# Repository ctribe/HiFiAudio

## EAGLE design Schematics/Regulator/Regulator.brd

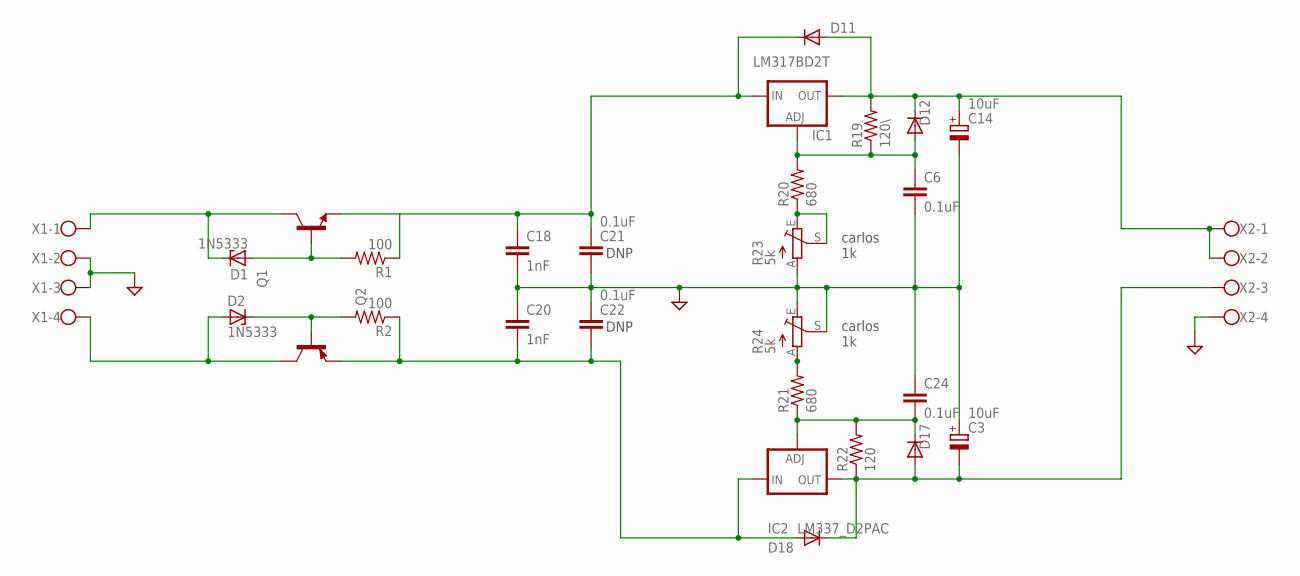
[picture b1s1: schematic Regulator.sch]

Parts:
C3, C14: 10uF; E2,5-6
C6, C21, C22, C24: 0.1uF; C025-025X050
C18, C20: 1nF; C025-025X050
D1, D2: 1N5333; C1702-15
D11, D12, D17, D18: 1N4004
IC1: LM317BD2T; D2PACK
IC2: LM337_D2PAC; D2PACK
Q1: -NPN-TO220V; TO220V
Q2: -PNP-TO220V; TO220V
R1, R2: 100; 0309/12
R19: 120\; 0309V
R20, R21: 680; 0309V
R22: 120; 0309V
R23, R24: 5k; B25P
X1, X2: W237-4

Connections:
GND: C3.+, C6.2, C14.-, C18.2, C20.1, C21.2, C22.1, C24.1, R23.A, R24.E, R24.S, X1.2, X1.3, X2.4
unnamed: D1.A, Q1.1 (B), R1.2
unnamed: C24.2, D17.C, IC2.1 (ADJ), R21.1, R22.2
unnamed: D1.C, Q1.2 (C), X1.1
unnamed: D2.C, Q2.1 (B), R2.2
unnamed: D2.A, Q2.2 (C), X1.4
unnamed: R20.1, R23.E, R23.S
unnamed: R21.2, R24.A
unnamed: C6.1, D12.A, IC1.1 (ADJ), R19.1, R20.2
V15+: C14.+, D11.A, D12.C, IC1.2 (OUT), R19.2, X2.1, X2.2
V15-: C3.-, D17.A, D18.C, IC2.2 (OUT), R22.1, X2.3
V15UN: C18.1, C21.1, D11.C, IC1.3 (IN), Q1.3 (E), R1.1
V-15UN: C20.2, C22.2, D18.A, IC2.3 (IN), Q2.3 (E), R2.1

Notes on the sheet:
DNP
carlos 1k

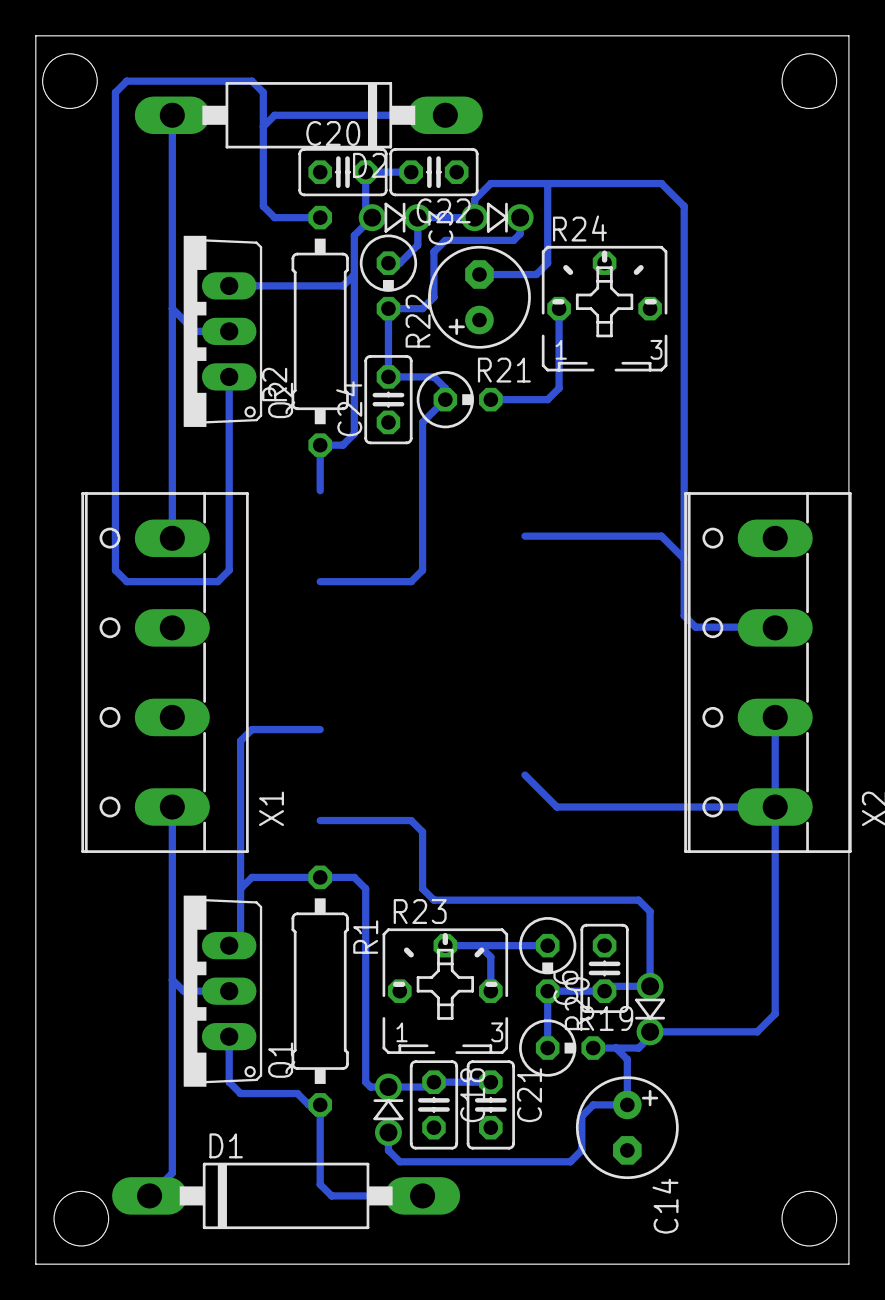
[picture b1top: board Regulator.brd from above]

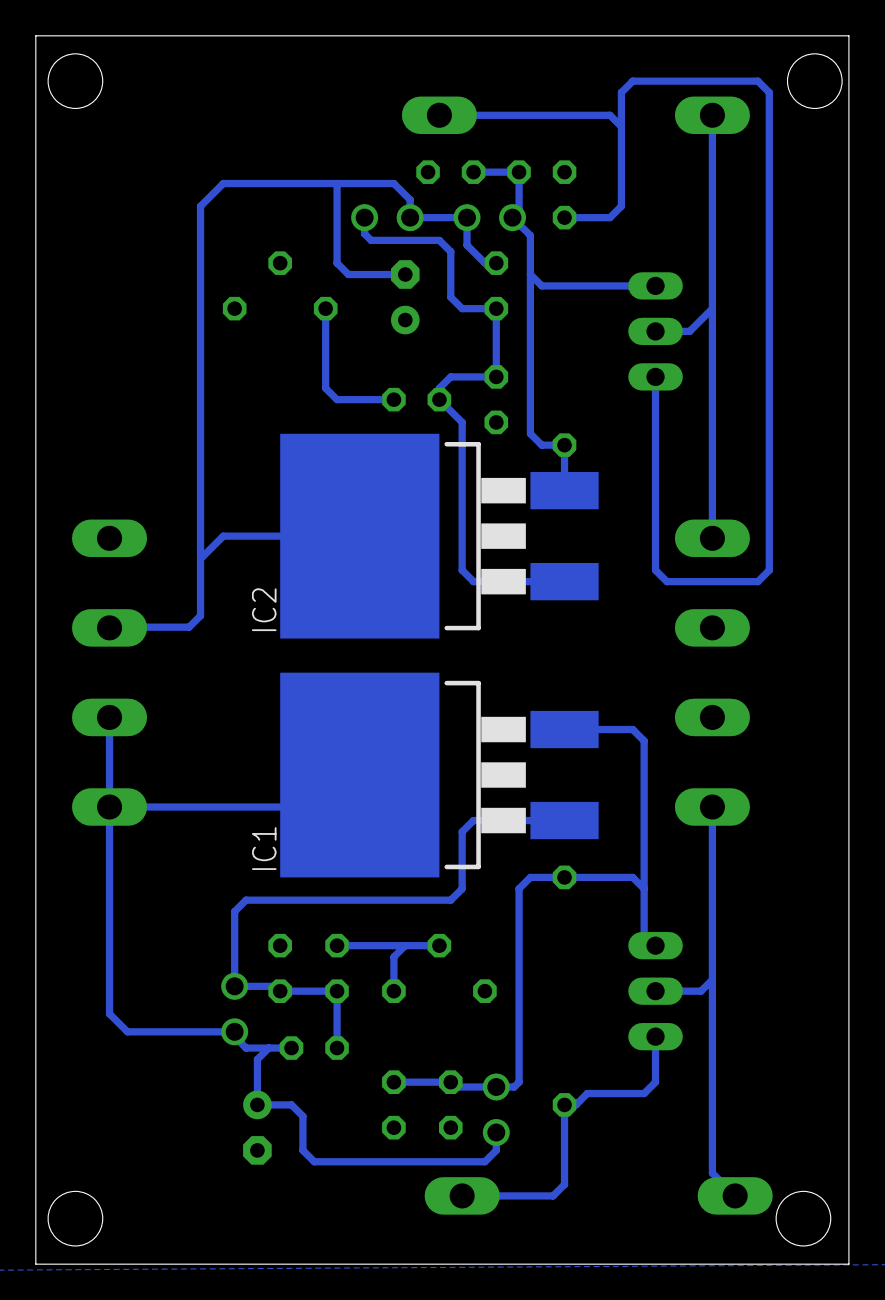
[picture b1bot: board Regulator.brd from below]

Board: 2 copper layers, 45.4 x 68.6 mm, 28 parts (2 on the bottom side), 13 nets.

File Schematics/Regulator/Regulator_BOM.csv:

"Qty";"Value";"Device";"Package";"Parts";"Description";"MF";"MPN";"OC_FARNELL";"OC_NEWARK";
"1";"";"-NPN-TO220V";"TO220V";"Q1";"NPN Transistror";"";"";"";"";
"1";"";"-PNP-TO220V";"TO220V";"Q2";"PNP Transistror";"";"";"";"";
"2";"";"W237-4";"W237-4";"X1, X2";"WAGO SCREW CLAMP";"";"";"unknown";"unknown";
"2";"0.1uF";"C-EU025-025X050";"C025-025X050";"C21, C22";"CAPACITOR, European symbol";"";"";"";"";
"2";"100";"R-US_0309/12";"0309/12";"R1, R2";"RESISTOR, American symbol";"";"";"";"";
"2";"10uF";"C-EU025-025X050";"C025-025X050";"C6, C24";"CAPACITOR, European symbol";"";"";"";"";
"2";"10uF";"CPOL-EUE2.5-6";"E2,5-6";"C3, C14";"POLARIZED CAPACITOR, European symbol";"";"";"";"";
"1";"120";"R-US_0309/V";"0309V";"R22";"RESISTOR, American symbol";"";"";"";"";
"1";"120\";"R-US_0309/V";"0309V";"R19";"RESISTOR, American symbol";"";"";"";"";
"4";"1N4004";"1N4004";"1N4004";"D11, D12, D17, D18";"";"";"";"";"";
"2";"1N5333";"1N5333";"C1702-15";"D1, D2";"Z DIODE";"";"";"";"";
"2";"1nF";"C-EU025-025X050";"C025-025X050";"C18, C20";"CAPACITOR, European symbol";"";"";"";"";
"2";"5k";"TRIM_EU-B25P";"B25P";"R23, R24";"POTENTIOMETER";"";"";"";"";
"2";"680";"R-US_0309/V";"0309V";"R20, R21";"RESISTOR, American symbol";"";"";"";"";
"1";"LM317BD2T";"LM317BD2T";"D2PACK";"IC1";"500 mA Adjustable Output Positive Voltage Regulator";"";"";"";"";
"1";"LM337_D2PAC";"LM337_D2PAC";"D2PACK";"IC2";"";"";"";"";"";

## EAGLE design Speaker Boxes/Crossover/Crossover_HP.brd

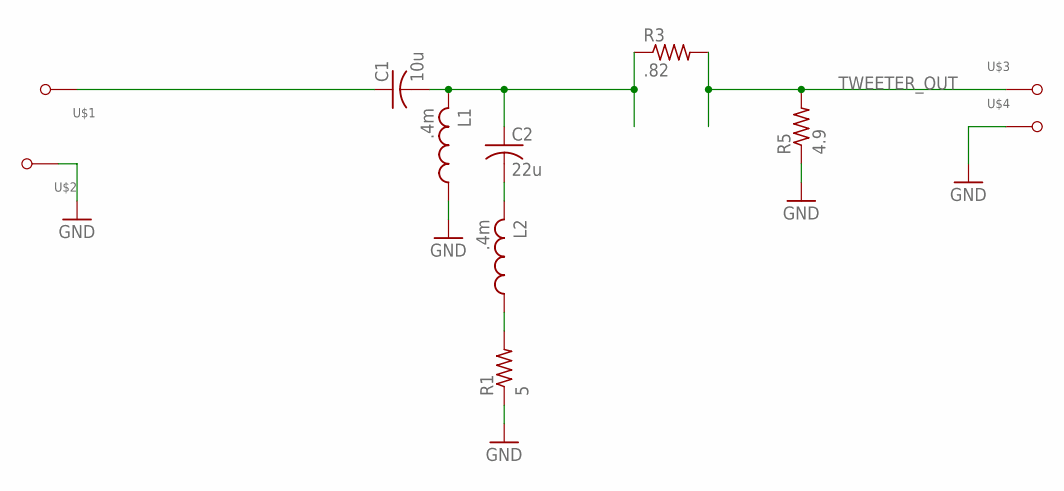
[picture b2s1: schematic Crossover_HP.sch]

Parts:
C1: 10u; 3.5MMP_8MMP
C2: 22u; 5MMP_10MMD
L1, L2: .4m; AIR_COIL_2INX3/4IN
R1: 5; 9.5MMX9MMX22MM
R3: .82; 9.5MMX9MMX48MM
R5: 4.9; 9.5MMX9MMX48MM
U$1, U$2, U$3, U$4: 18AWG_HOLE

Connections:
GND: L1.P$1 (1), R1.P$1 (1), R5.P$1 (1), U$2.P$1, U$4.P$1
unnamed: C1.NEG (2), C2.POS (1), L1.P$2 (2), R3.P$1 (1)
unnamed: C2.NEG (2), L2.P$2 (2)
unnamed: L2.P$1 (1), R1.P$2 (2)
unnamed: C1.POS (1), U$1.P$1
TWEETER_OUT: R3.P$2 (2), R5.P$2 (2), U$3.P$1

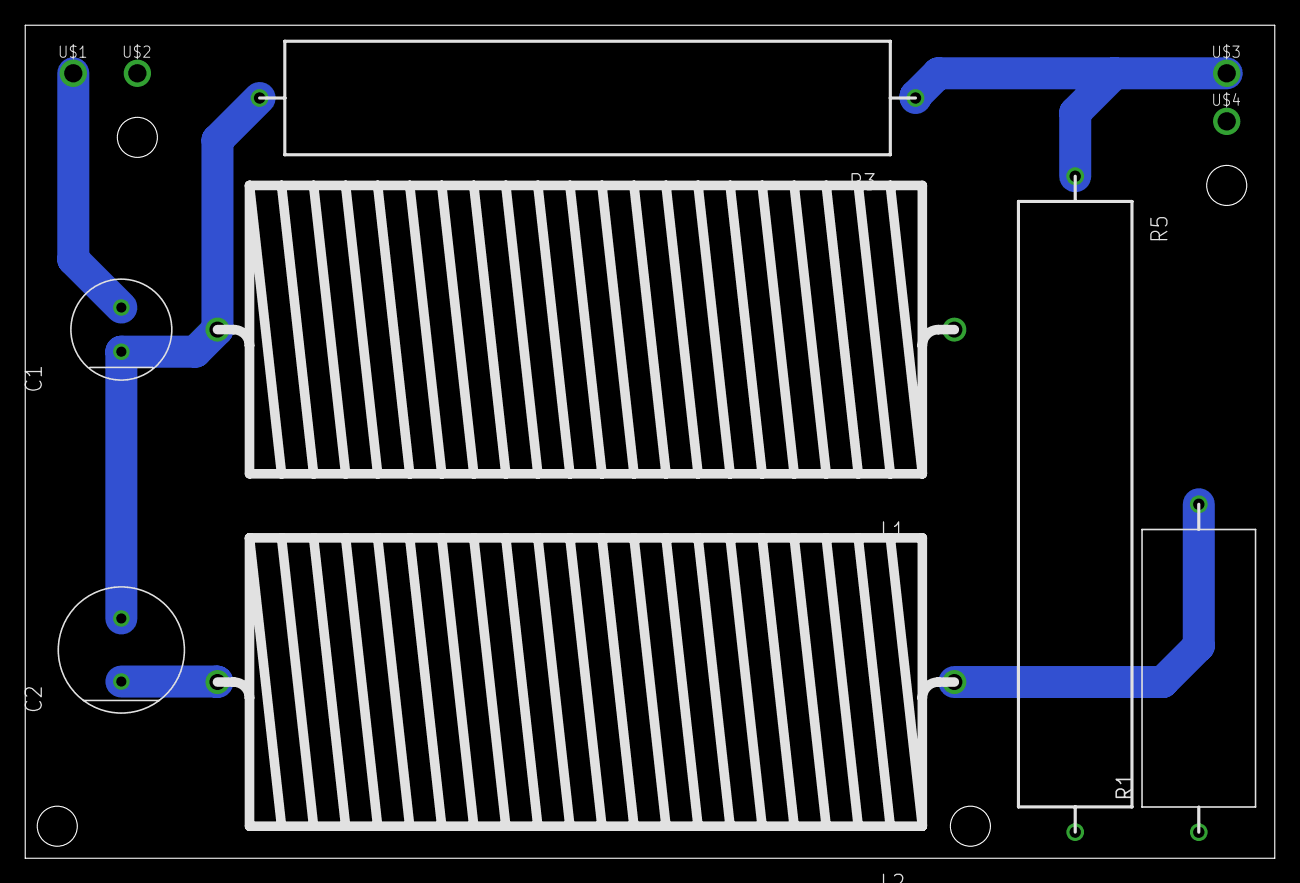
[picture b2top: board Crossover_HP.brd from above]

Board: 2 copper layers, 99.1 x 66.0 mm, 11 parts (0 on the bottom side), 6 nets.

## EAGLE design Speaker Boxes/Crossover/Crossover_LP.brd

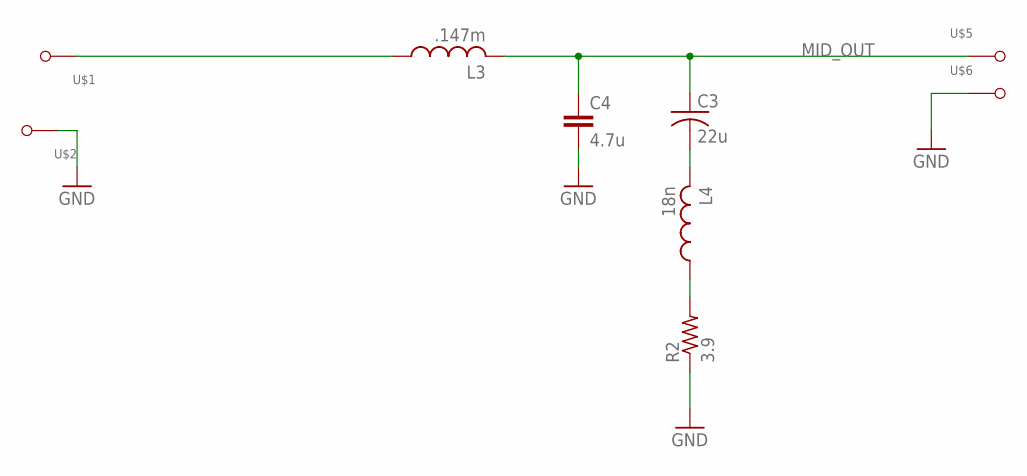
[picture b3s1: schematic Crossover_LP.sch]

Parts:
C3: 22u; 5MMP_10MMD
C4: 4.7u; C225-074X268
L3: .147m; AIR_COIL_2INX3/4IN
L4: 18n; AIR_COIL_2INX3/4IN
R2: 3.9; 9.5MMX9MMX22MM
U$1, U$2, U$5, U$6: 18AWG_HOLE

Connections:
GND: C4.2, R2.P$1 (1), U$2.P$1, U$6.P$1
MID_OUT: C3.POS (1), C4.1, L3.P$2 (2), U$5.P$1
unnamed: L3.P$1 (1), U$1.P$1
unnamed: C3.NEG (2), L4.P$2 (2)
unnamed: L4.P$1 (1), R2.P$2 (2)

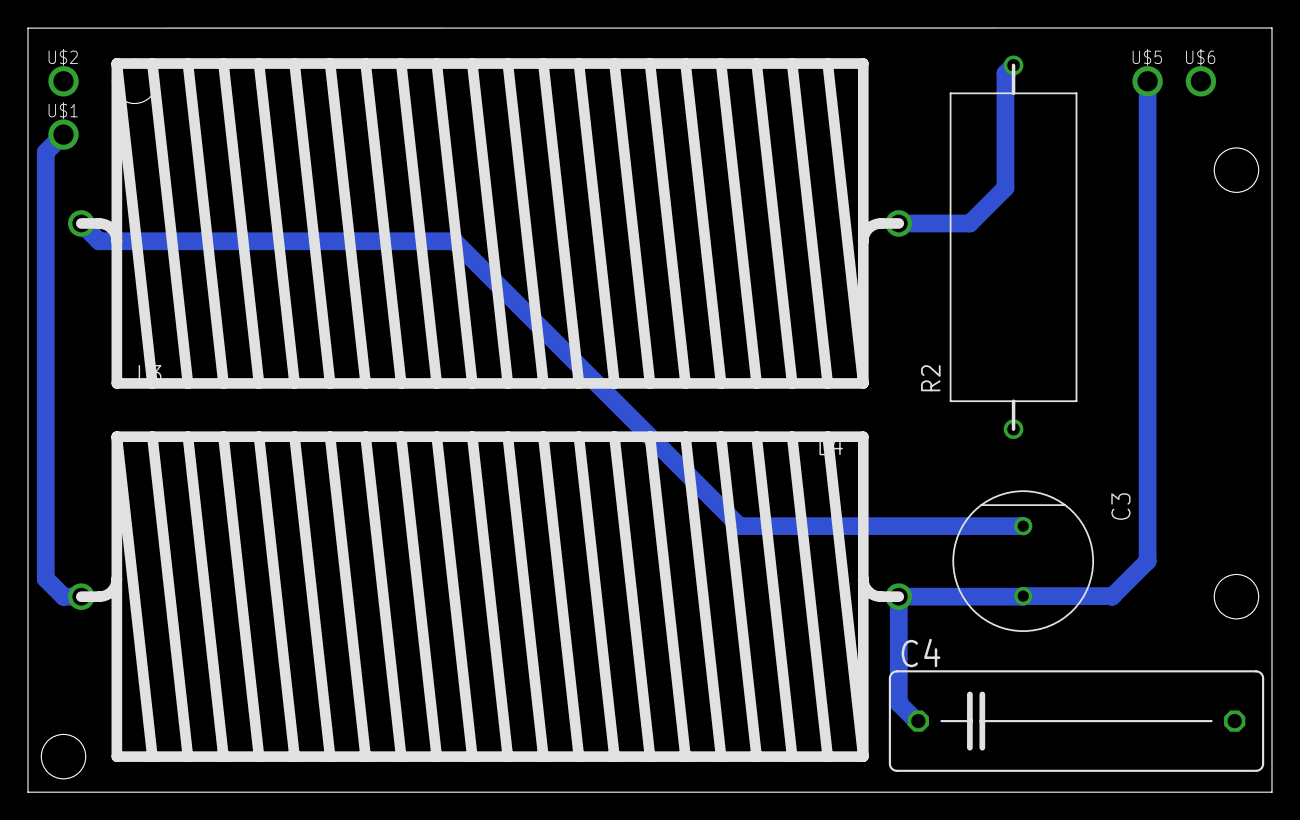
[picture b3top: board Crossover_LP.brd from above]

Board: 2 copper layers, 88.9 x 54.6 mm, 9 parts (0 on the bottom side), 5 nets.

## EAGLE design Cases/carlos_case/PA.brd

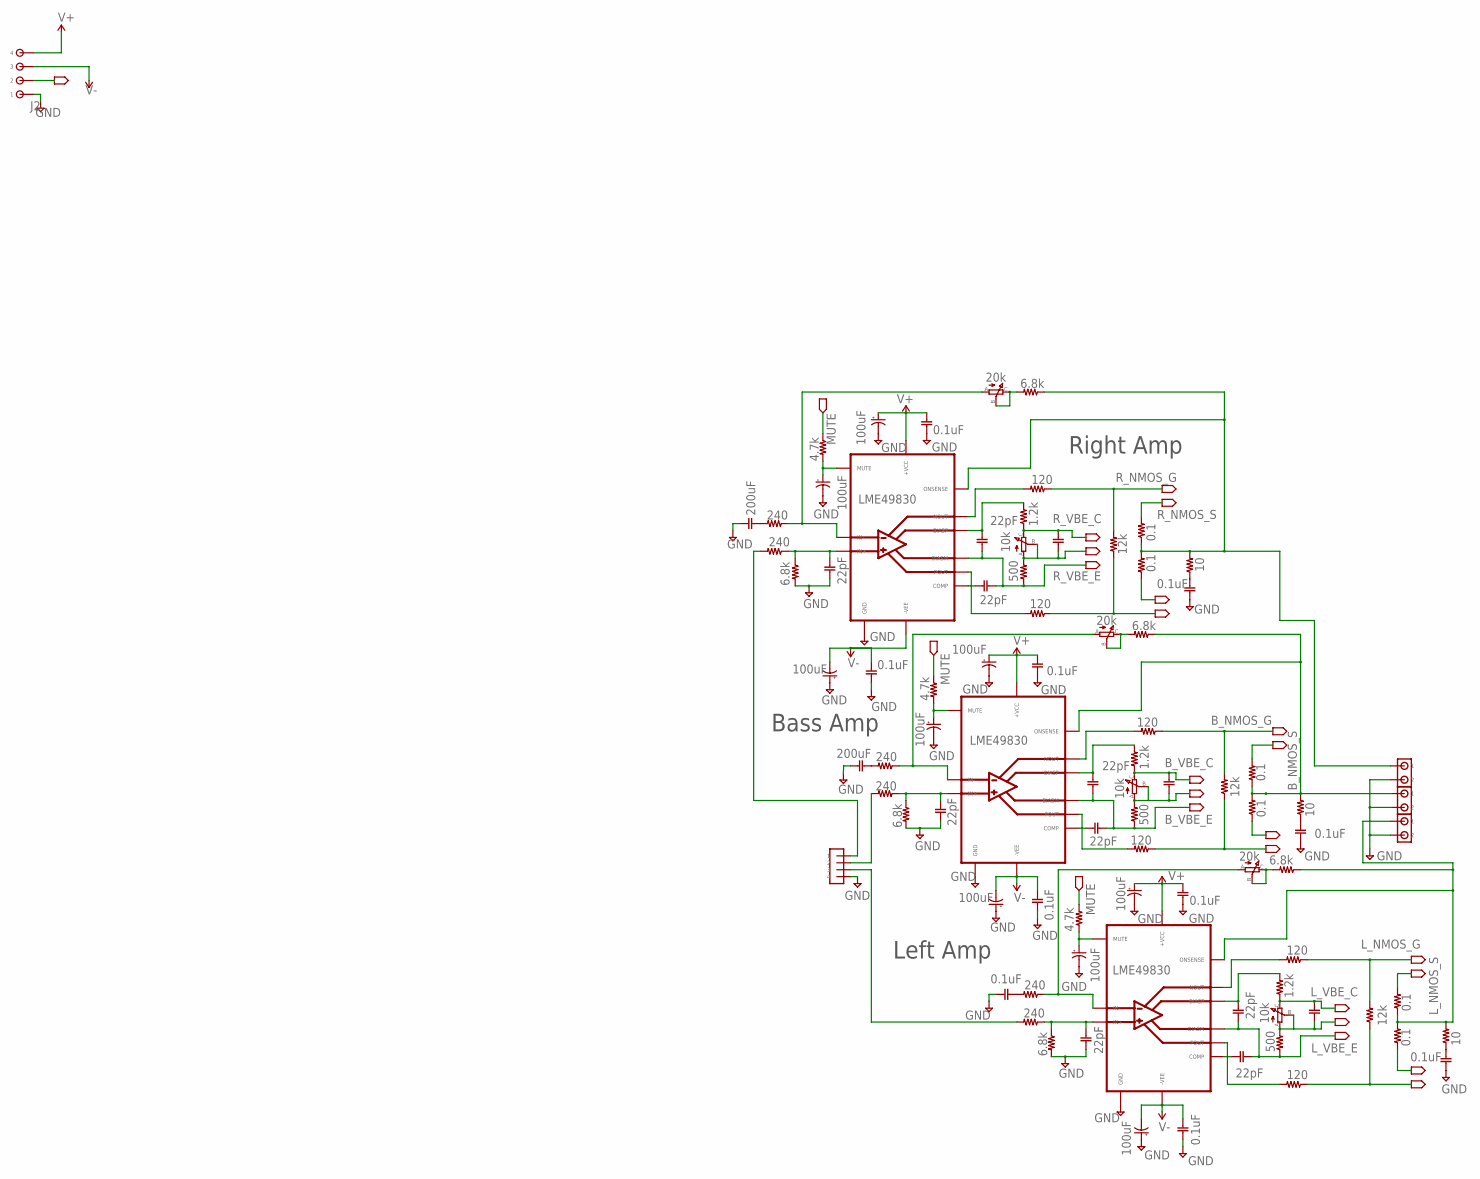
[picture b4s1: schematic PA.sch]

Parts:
C1, C8, C9, C10, C20, C21, C22, C29, C35, C36, C37, C44: 22pF; C050-024X044
C2, C4, C6, C16, C17, C28, C31, C32, C43: 100uF; E2,5-6
C3, C5, C15, C18, C19, C27, C33, C34, C42, C45: 0.1uF; C050-024X044
C7, C30: 200uF; C050-024X044
J1: 4_PIN_AMPCONN; 4_PIN_AMPCON
J2: 1984633
J3, J4, J5: 2TERMINAL_SPEAKER
PR1, PR2, PR3, PR4, PR5, PR6: 0.1; 0617V
R1, R11, R12, R22, R23, R55: 240; 0204V
R2, R10, R13, R21, R24, R56: 6.8k; 0204V
R3, R14, R44: 1.2k; 0204V
R4, R15, R45: 500; 0204V
R5, R16, R46: 12k; 0204V
R6, R7, R17, R18, R47, R48: 120; 0204V
R8, R19, R51: 10; 0309V
R9, R20, R52: 4.7k; 0204V
U1, U2, U3: LME49830; NDN0015A
VR1, VR3, VR5: 20k; EVM2W
VR2, VR4, VR6: 10k; EVM2W

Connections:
BASS_OUT: J4.P$1 (1), PR1.2, PR2.1, R8.2, R13.1, U2.P$8 (ONSENSE)
B_NMOS_G: R5.2, R7.1
B_NMOS_S: PR2.2
B_PMOS_G: R5.1, R6.1
B_PMOS_S: PR1.1
B_VBE_B: C21.1, R4.2, VR4.A, VR4.B
B_VBE_C: C21.2, R3.1, VR4.C
B_VBE_E: C20.1, C22.1, R4.1, U2.P11 (BIASM)
GND: C1.1, C2.+, C3.1, C4.-, C5.2, C6.-, C7.1, C15.1, C16.+, C17.-, C18.1, C19.2, C27.1, C28.-, C29.1, C30.1, C31.+, C32.-, C33.1, C34.2, C42.1, C43.-, C44.1, C45.1, J1.4, J2.P$1 (1), J3.P$2 (2), J4.P$2 (2), J5.P$2 (2), R2.2, R10.2, R21.2, U1.P3 (GND), U2.P3 (GND), U3.P3 (GND)
LEFT_IN: J1.3, R22.2
LEFT_OUT: J5.P$1 (1), PR3.2, PR4.1, R19.2, R24.1, U3.P$8 (ONSENSE)
L_NMOS_G: R16.2, R18.1
L_NMOS_S: PR4.2
L_PMOS_G: R16.1, R17.1
L_PMOS_S: PR3.1
L_VBE_B: C36.1, R15.2, VR6.A, VR6.B
L_VBE_C: C36.2, R14.1, VR6.C
L_VBE_E: C35.1, C37.1, R15.1, U3.P11 (BIASM)
MUTE: J2.P$2 (2), R9.1, R20.1, R52.1
unnamed: J1.2, R11.2
unnamed: J1.1, R1.2
unnamed: C20.2, R3.2, U2.P12 (BIASP)
unnamed: R48.2, U1.P14 (NOUT)
unnamed: C22.2, U2.P6 (COMP)
unnamed: R6.2, U2.P13 (POUT)
unnamed: C27.2, R8.1
unnamed: C28.+, R9.2, U2.P2 (MUTE)
unnamed: R7.2, U2.P14 (NOUT)
unnamed: C1.2, R1.1, R2.1, U1.P4 (IN+)
unnamed: C29.2, R10.1, R11.1, U2.P4 (IN+)
unnamed: C30.2, R12.2
unnamed: R12.1, U2.P5 (IN-), VR3.A
unnamed: R13.2, VR3.B, VR3.C
unnamed: C35.2, R14.2, U3.P12 (BIASP)
unnamed: C37.2, U3.P6 (COMP)
unnamed: R17.2, U3.P13 (POUT)
unnamed: R55.1, U1.P5 (IN-), VR1.A
unnamed: C42.2, R19.1
unnamed: C7.2, R55.2
unnamed: C43.+, R20.2, U3.P2 (MUTE)
unnamed: R18.2, U3.P14 (NOUT)
unnamed: C44.2, R21.1, R22.1, U3.P4 (IN+)
unnamed: R56.2, VR1.B, VR1.C
unnamed: C45.2, R23.2
unnamed: R23.1, U3.P5 (IN-), VR5.A
unnamed: R24.2, VR5.B, VR5.C
unnamed: C8.2, U1.P6 (COMP)
unnamed: C9.2, R44.2, U1.P12 (BIASP)
unnamed: R47.2, U1.P13 (POUT)
unnamed: C15.2, R51.1
unnamed: C6.+, R52.2, U1.P2 (MUTE)
RIGHT_OUT: J3.P$1 (1), PR5.2, PR6.1, R51.2, R56.1, U1.P$8 (ONSENSE)
R_NMOS_G: R46.2, R48.1
R_NMOS_S: PR6.2
R_PMOS_G: R46.1, R47.1
R_PMOS_S: PR5.1
R_VBE_B: C10.1, R45.2, VR2.A, VR2.B
R_VBE_C: C10.2, R44.1, VR2.C
R_VBE_E: C8.1, C9.1, R45.1, U1.P11 (BIASM)
V+: C4.+, C5.1, C17.+, C19.1, C32.+, C34.1, J2.P$4 (4), U1.P15 (+VCC), U2.P15 (+VCC), U3.P15 (+VCC)
V-: C2.-, C3.2, C16.-, C18.2, C31.-, C33.2, J2.P$3 (3), U1.P10 (-VEE), U2.P10 (-VEE), U3.P10 (-VEE)

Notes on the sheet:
Right Amp
Bass Amp
Left Amp

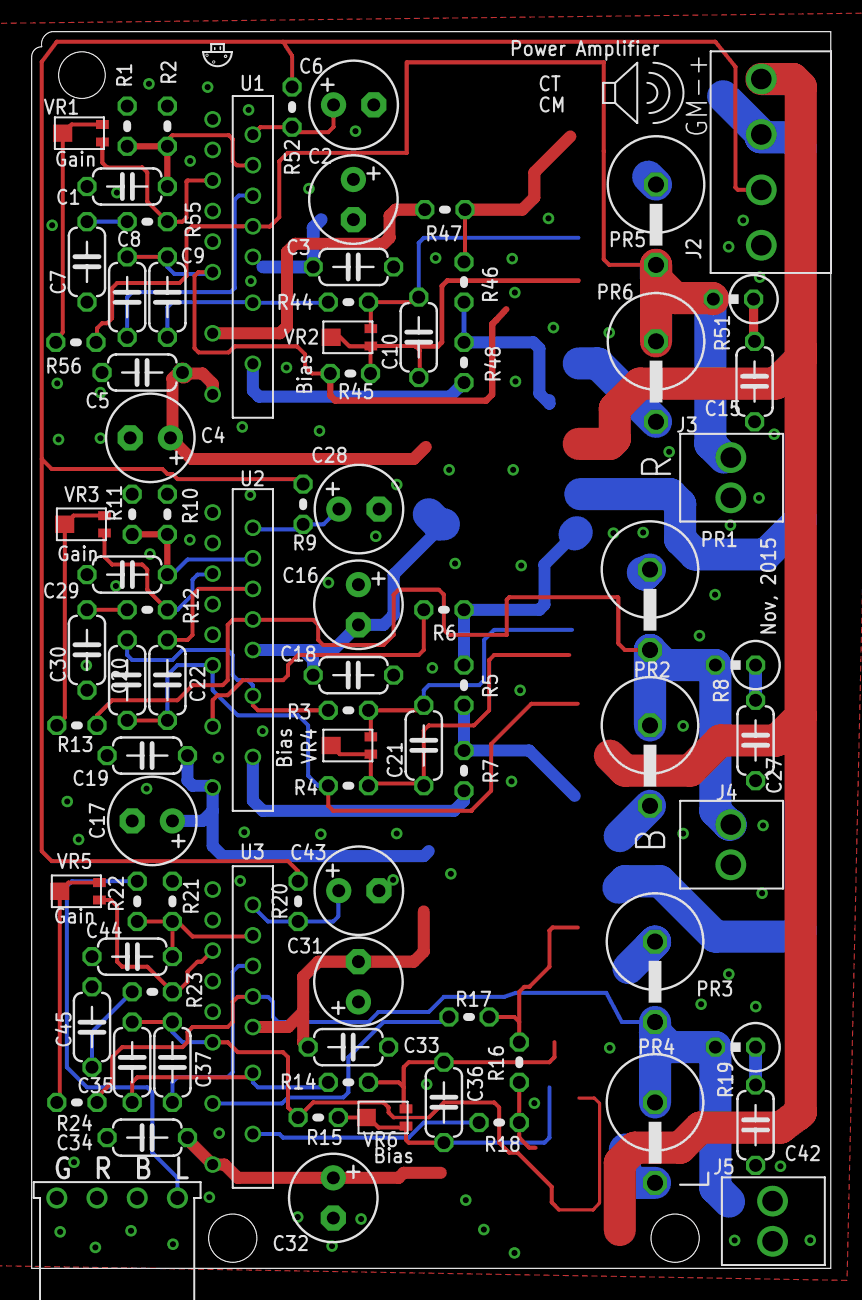
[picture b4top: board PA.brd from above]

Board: 2 copper layers, 50.5 x 78.1 mm, 88 parts (0 on the bottom side), 55 nets.

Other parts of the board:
U$17: MUSHROOM
U$48: SPEAKER

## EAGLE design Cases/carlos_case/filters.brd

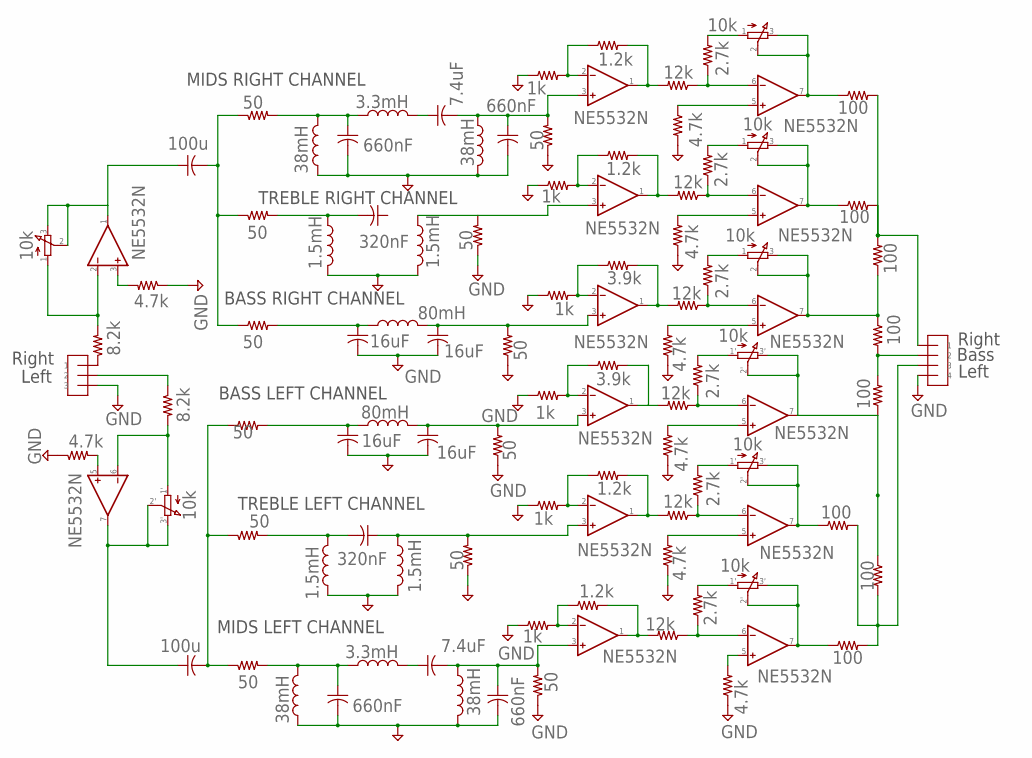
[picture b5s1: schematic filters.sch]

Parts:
C1, C10: 7.4uF; C050-024X044
C2, C3, C11, C12: 660nF; C050-024X044
C4, C9: 320nF; C050-024X044
C5, C6, C7, C8: 16uF; C050-024X044
C13, C14: 100u; C050-024X044
IC1, IC2, IC3, IC4, IC5, IC6, IC7: NE5532N; DIL08
J1: 3_PIN_AMPCONN
J2: 4_PIN_AMPCONN; 4_PIN_AMPCON
L1, L10: 3.3mH; 6000-XXXX-RC
L2, L3, L11, L12: 38mH; 6000-XXXX-RC
L4, L5, L8, L9: 1.5mH; 6000-XXXX-RC
L6, L7: 80mH; 6000-XXXX-RC
R1, R2: 8.2k; 0204V
R3, R4, R9, R10, R14, R15, R22, R23, R27, R28, R31, R32: 50; 0204V
R5, R7, R13, R20, R26, R38: 1k; 0204V
R6, R11, R16, R19, R24, R33: 12k; 0204V
R8, R21: 3.9k; 0204V
R12, R17, R25, R36: 1.2k; 0204V
R18, R29, R30, R34, R35, R37: 2.7k; 0204V
R39, R40, R41, R88, R89, R90, R91, R92: 100; 0204V
R42, R43, R44, R45, R46, R47, R48, R49: 4.7k; 0204V
VR1: 10k; VOL_POT_2GANG
VR2, VR3, VR4: 10k; TONE_POT_2GANG

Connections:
BASS: J2.2, R41.2, R90.2
GND: C2.2, C3.2, C5.2, C6.2, C7.2, C8.2, C11.2, C12.2, J1.3, J2.4, L2.1, L3.2, L4.2, L5.2, L8.1, L9.2, L11.2, L12.1, R3.1, R5.1, R7.1, R10.1, R13.1, R15.1, R20.1, R23.1, R26.1, R28.1, R31.1, R38.1, R42.1, R43.1, R44.2, R45.1, R46.1, R47.1, R48.1, R49.1
LEFT: J2.3, R39.2, R91.2, R92.2
LEFT_IN: J1.2, R2.1
MVO: IC6.7 (OUT), R40.1, R90.1, VR4.2 (1_2), VR4.3 (1_3)
unnamed: IC1.2 (-IN), R1.2, VR1.1
unnamed: C13.1, IC1.1 (OUT), VR1.2, VR1.3
unnamed: IC1.6 (-IN), R2.2, VR1.1' (1)
unnamed: IC2.6 (-IN), R16.1, R18.1
unnamed: C14.1, IC1.7 (OUT), VR1.2' (2), VR1.3' (3)
unnamed: IC6.2 (-IN), R7.2, R8.1
unnamed: C6.1, IC6.3 (+IN), L6.2, R3.2
unnamed: IC3.6 (-IN), R33.1, R37.1
unnamed: IC4.2 (-IN), R12.1, R13.2
unnamed: IC7.1 (OUT), R19.2
unnamed: IC6.6 (-IN), R6.1, R34.1
unnamed: C5.1, L6.1, R4.2
unnamed: C4.2, L5.1, R9.2
unnamed: C8.1, IC7.3 (+IN), L7.2, R31.2
unnamed: IC2.1 (OUT), R16.2, R17.2
unnamed: IC1.3 (+IN), R42.2
unnamed: IC4.1 (OUT), R11.2, R12.2
unnamed: IC4.6 (-IN), R11.1, R35.1
unnamed: IC1.5 (+IN), R43.2
unnamed: IC2.7 (OUT), R88.1, VR2.2 (1_2), VR2.3 (1_3)
unnamed: C13.2, R4.1, R9.1, R14.1
unnamed: C2.1, L1.1, L2.2, R14.2
unnamed: R18.2, VR2.1 (1_1)
unnamed: IC7.6 (-IN), R19.1, R29.1
unnamed: IC2.2 (-IN), R5.2, R17.1
unnamed: IC2.5 (+IN), R44.1
unnamed: C1.1, L1.2
unnamed: C9.2, L8.2, R22.2
unnamed: IC5.5 (+IN), R48.2
unnamed: IC5.1 (OUT), R24.2, R25.2
unnamed: IC5.6 (-IN), R24.1, R30.1
unnamed: C11.1, L10.1, L12.2, R27.2
unnamed: C10.1, L10.2
unnamed: IC4.5 (+IN), R45.2
unnamed: R29.2, VR4.1' (1_1)
unnamed: IC6.5 (+IN), R46.2
unnamed: IC7.7 (OUT), R39.1, R41.1, VR4.2' (1_2), VR4.3' (1_3)
unnamed: IC5.7 (OUT), R91.1, VR3.2' (1_2), VR3.3' (1_3)
unnamed: R30.2, VR3.1' (1_1)
unnamed: C7.1, L7.1, R32.2
unnamed: IC7.2 (-IN), R20.2, R21.1
unnamed: IC5.2 (-IN), R25.1, R26.2
unnamed: IC3.1 (OUT), R33.2, R36.2
unnamed: IC3.5 (+IN), R49.2
unnamed: IC7.5 (+IN), R47.2
unnamed: IC3.7 (OUT), R92.1, VR2.2' (1_2), VR2.3' (1_3)
unnamed: R34.2, VR4.1 (1_1)
unnamed: IC4.7 (OUT), R89.1, VR3.2 (1_2), VR3.3 (1_3)
unnamed: R35.2, VR3.1 (1_1)
unnamed: R37.2, VR2.1' (1_1)
unnamed: IC3.2 (-IN), R36.1, R38.2
unnamed: C10.2, C12.1, IC3.3 (+IN), L11.1, R28.2
unnamed: C14.2, R22.1, R27.1, R32.1
unnamed: C9.1, IC5.3 (+IN), L9.1, R23.2
unnamed: IC4.3 (+IN), L4.1, R10.2
unnamed: IC6.1 (OUT), R6.2, R8.2
unnamed: C1.2, C3.1, IC2.3 (+IN), L3.1, R15.2
RIGHT: J2.1, R40.2, R88.2, R89.2
RIGHT_IN: J1.1, R1.1
V+: IC1.8 (V+), IC2.8 (V+), IC3.8 (V+), IC4.8 (V+), IC5.8 (V+), IC6.8 (V+), IC7.8 (V+)
V-: IC1.4 (V-), IC2.4 (V-), IC3.4 (V-), IC4.4 (V-), IC5.4 (V-), IC6.4 (V-), IC7.4 (V-)

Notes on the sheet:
BASS RIGHT CHANNEL
TREBLE RIGHT CHANNEL
MIDS RIGHT CHANNEL
BASS LEFT CHANNEL
TREBLE LEFT CHANNEL
MIDS LEFT CHANNEL
Left
Right
Bass

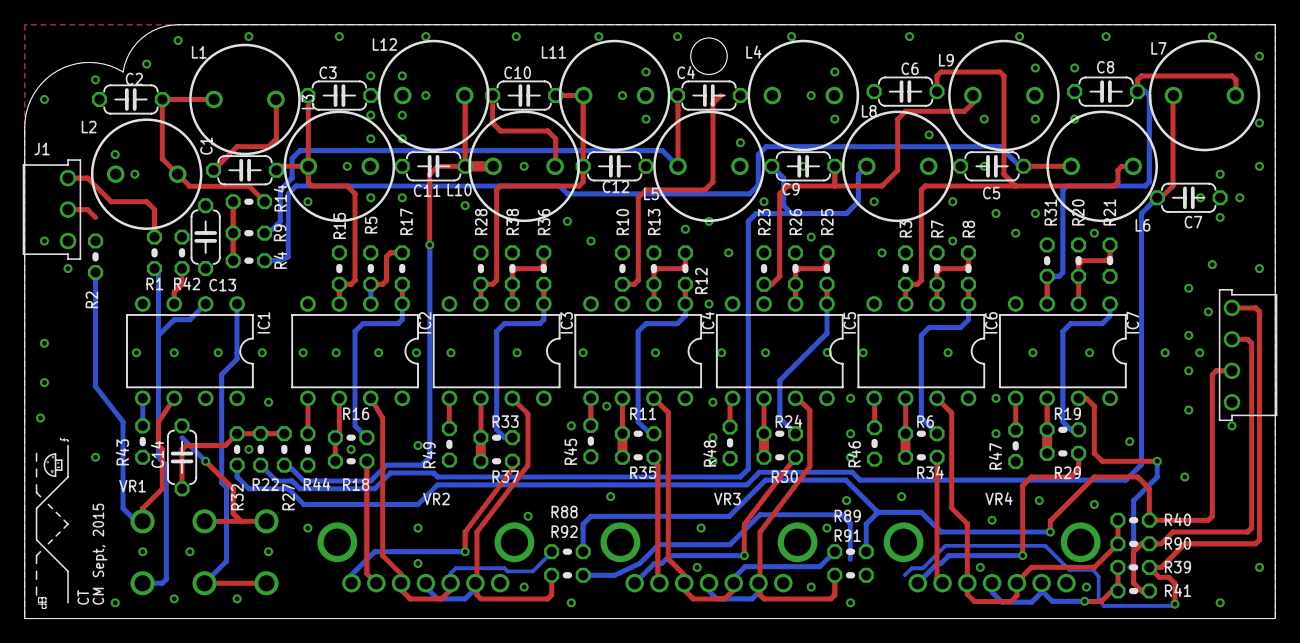
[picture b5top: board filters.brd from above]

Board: 2 copper layers, 101.0 x 47.9 mm, 95 parts (0 on the bottom side), 66 nets.

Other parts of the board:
U$1: MUSHROOM
U$2: BODE

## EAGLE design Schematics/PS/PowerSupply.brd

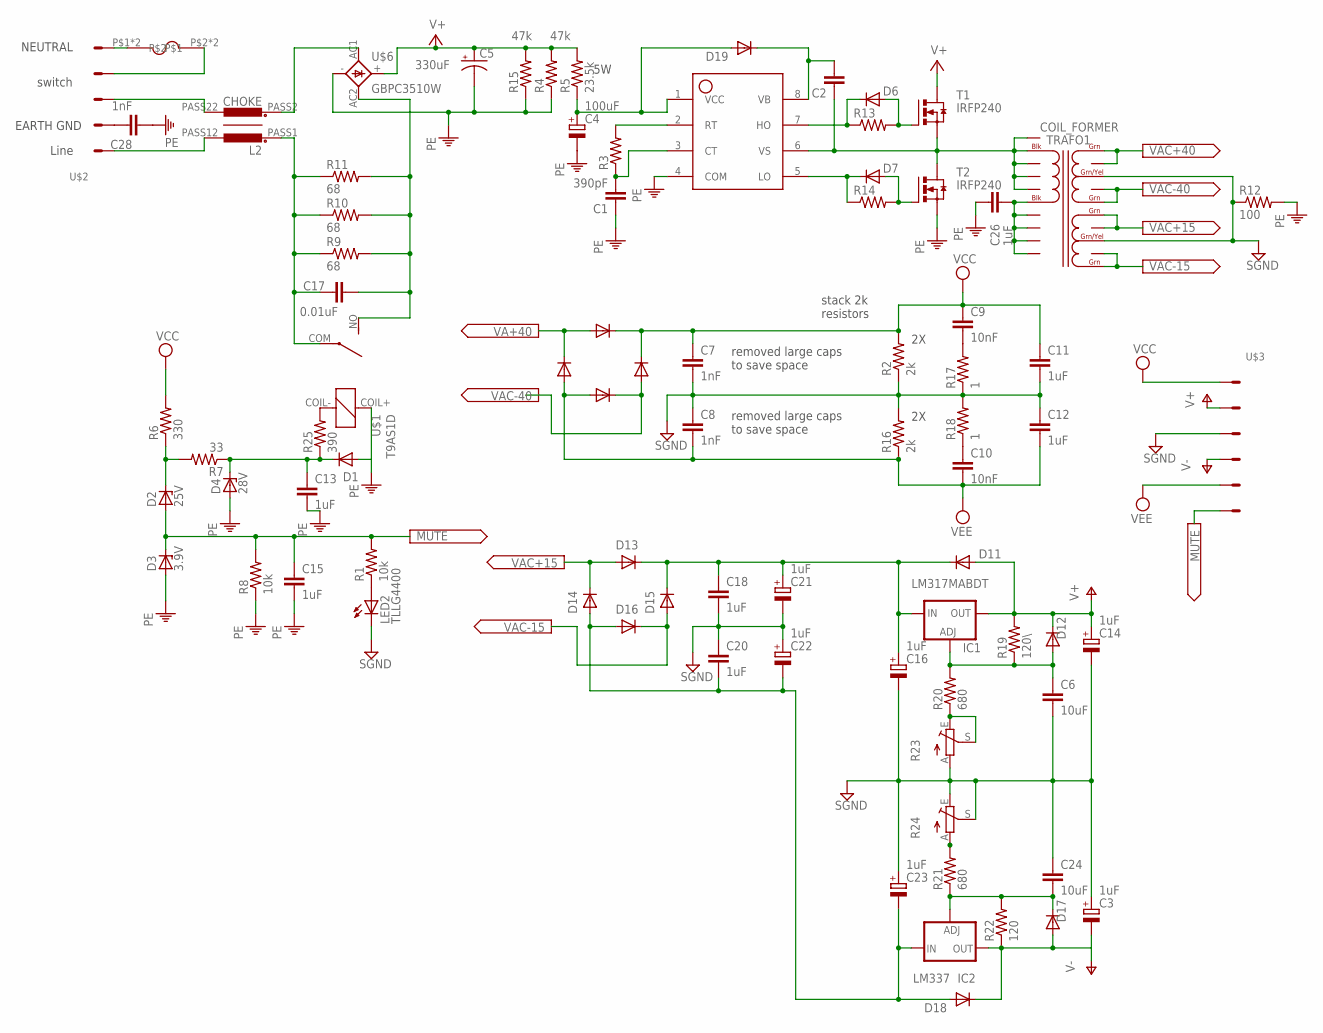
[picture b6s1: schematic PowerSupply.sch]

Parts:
C1: 390pF; C025-025X050
C2: C-EU050-035X075; C050-035X075
C3, C14, C16, C21, C22, C23: 1uF; E2,5-6
C4: 100uF; E2,5-6
C5: 330uF; E7,5-18
C6, C24: 10uF; C025-025X050
C7, C8: 1nF; C102-064X133
C9, C10: 10nF; C102-064X133
C11, C12, C13, C15, C18, C20: 1uF; C102-064X133
C17: 0.01uF; C075-042X103
C26: 1uF; C025-025X050
C28: 1nF; C0805K
D1, D6, D7, D11, D12, D13, D14, D15, D16, D17, D18, D19: 1N4004
D2: 25V; P1Z12
D3: 3.9V; ZDIO-2.5
D4: 28V; P1Z12
D5, D8, D9, D10: VS-ETL1506-M3
IC1: LM317MABDT; DPACK
IC2: LM337
L2: CHOKE
LED2: TLLG4400; LED3MM
R1, R8: 10k; 0204V
R2, R16: 2k; VTA52
R3, R13, R14: R-US_0204/2V; 0204V
R4, R15: 47k; 0617V
R5: 23.5k; 0617V
R6: 330; 0309V
R7: 33; 0309V
R9, R10, R11: 68; 0617V
R12: 100; 0207/15
R17, R18: 1; 0411/12
R19: 120\; 0204V
R20, R21: 680; 0204V
R22: 120; 0204V
R23, R24: TRIM_EU-B25P; B25P
R25: 390; 0204V
T1, T2: IRFP240
TRAFO1: COIL_FORMER
U$1: T9AS1D; RELAY_CM
U$2: SCREW_TERMINAL_5
U$3: SCREW_TERMINAL_6
U$4: FUSE; FUSE_PADS
U$5: IRS2153D
U$6: GBPC3510W

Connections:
EGND: C28.1, U$2.P$3 (S2)
GND: C1.1, C4.-, C5.-, C13.2, C15.2, C26.1, C28.2, D1.A, D3.A, D4.A, R4.1, R8.1, R12.2, R15.1, T2.S, U$1.COIL+, U$5.4 (COM), U$6.-
LINE: L2.PASS12, U$2.P$2 (S1)
MUTE: C15.1, D2.A, D3.C, R1.2, R8.2, U$3.P$6 (S6)
unnamed: LED2.A, R1.1
unnamed: C24.2, D17.C, IC2.1 (ADJ), R21.1, R22.2
unnamed: L2.PASS2, U$6.AC1
unnamed: C2.2, D19.C, U$5.8 (VB)
unnamed: C1.2, R3.1, U$5.3 (CT)
unnamed: C9.2, R17.2
unnamed: C26.2, TRAFO1.P$6 (P2), TRAFO1.P$7 (P22), TRAFO1.P$8 (P23), TRAFO1.P$9 (P24), TRAFO1.P$10 (P25)
unnamed: R25.2, U$1.COIL-
unnamed: D2.C, R6.1, R7.2
unnamed: R3.2, U$5.2 (RT)
unnamed: D6.C, R13.1, U$5.7 (HO)
unnamed: R20.1, R23.E, R23.S
unnamed: C13.1, D1.C, D4.C, R7.1, R25.1
unnamed: C4.+, D19.A, R5.1, U$5.1 (VCC)
unnamed: C17.2, R9.2, R10.2, R11.2, U$1.NO, U$6.AC2
unnamed: D6.A, R13.2, T1.G
unnamed: D7.C, R14.1, U$5.5 (LO)
unnamed: D7.A, R14.2, T2.G
unnamed: C2.1, T1.S, T2.D, TRAFO1.P$1 (P1), TRAFO1.P$2 (P12), TRAFO1.P$3 (P13), TRAFO1.P$4 (P14), TRAFO1.P$5 (P15), U$5.6 (VS)
unnamed: R21.2, R24.A
unnamed: C10.1, R18.1
unnamed: C6.1, D12.A, IC1.1 (ADJ), R19.1, R20.2
NUTRAL: U$2.P$6 (S5), U$4.P$1, U$4.P$3
SGND: C3.+, C6.2, C7.2, C8.1, C11.2, C12.1, C14.-, C16.-, C18.2, C20.1, C21.-, C22.+, C23.+, C24.1, LED2.K (C), R2.1, R12.1, R16.2, R17.1, R18.2, R23.A, R24.E, R24.S, TRAFO1.P$13 (GND30), TRAFO1.P$18 (GND15), U$3.P$3 (S3)
SOMENET: C17.1, L2.PASS1, R9.1, R10.1, R11.1, U$1.COM
SWITCH1: U$2.P$5 (S4), U$4.P$2, U$4.P$4
SWITCH2: L2.PASS22, U$2.P$4 (S3)
V15+: C14.+, D11.A, D12.C, IC1.4 (OUT), R19.2, U$3.P$2 (S2)
V15-: C3.-, D17.A, D18.C, IC2.3 (OUT), R22.1, U$3.P$4 (S4)
V15UN: C16.+, C18.1, C21.+, D11.C, D13.C, D15.C, IC1.3 (IN)
V+: C5.+, R4.2, R5.2, R15.2, T1.D, U$6.+
V-15UN: C20.2, C22.-, C23.-, D14.A, D16.A, D18.A, IC2.4 (IN)
VAC+15: D13.A, D14.C, TRAFO1.P$16 (SEC15+), TRAFO1.P$17 (S15+1)
VAC+40: D5.A, D8.C, TRAFO1.P$11 (SEC30V+), TRAFO1.P$12 (S30+1)
VAC-15: D15.A, D16.C, TRAFO1.P$19 (S15-1), TRAFO1.P$20 (SEC15-)
VAC-40: D9.A, D10.C, TRAFO1.P$14 (S30-1), TRAFO1.P$15 (SEC30-)
VCC: C7.1, C9.1, C11.1, D5.C, D9.C, R2.2, R6.2, U$3.P$1 (S1)
VEE: C8.2, C10.2, C12.2, D8.A, D10.A, R16.1, U$3.P$5 (S5)

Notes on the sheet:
Line
EARTH GND
NEUTRAL
switch
removed large caps to save space
stack 2k resistors

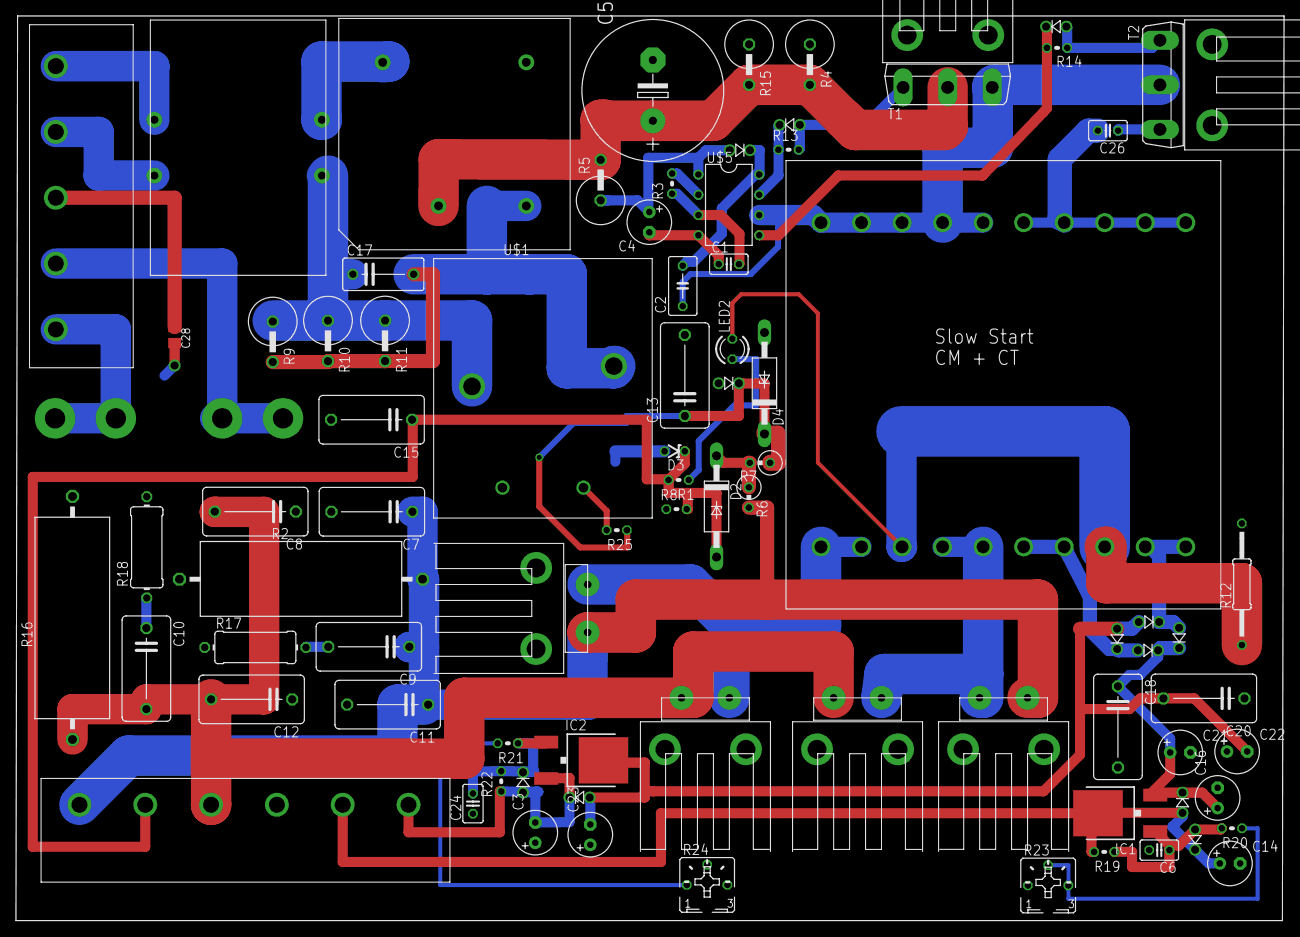
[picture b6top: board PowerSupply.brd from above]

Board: 2 copper layers, 159.0 x 113.4 mm, 82 parts (0 on the bottom side), 42 nets.
